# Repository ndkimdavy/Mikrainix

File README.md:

# Mikrainix

Mikrainix is a custom PCB design project for an embedded Linux mini PC based on the **Rockchip RV1106G3 MPU**, featuring integrated AI hardware acceleration and a **Lattice ECP5 FPGA** for programmable logic.

## MPU Specifications

- **CPU:** Single-core ARM Cortex-A7, up to 1.2 GHz.
- **Integrated MCU:** RISC-V architecture.
- **Memory:** 256 MB integrated DDR3L.
- **NPU:** 1 TOPS AI accelerator.
- **Interfaces:** USB 2.0, Ethernet, SDIO, UART, SPI, and I²C.

## FPGA Specifications

- **FPGA:** Lattice ECP5 LFE5U-25F-7BG256C.
- **Communication:** SPI interface with the Rockchip MPU and USB-UART interface.

## Board Architecture

The design also includes:

- An STM32L052 microcontroller for system management and control.
- An ESP32-MINI-1-N4 for Wi-Fi and Bluetooth connectivity.
- A USB-C Power Delivery interface for power management.
- A shared USB port between the MPU and FPGA.
- A dedicated FPGA subsystem with its own power supplies and communication interfaces.

## Project Status

**In progress** — schematic and PCB design phase.

## Author

**Kim Davy NDAYONGEJE**

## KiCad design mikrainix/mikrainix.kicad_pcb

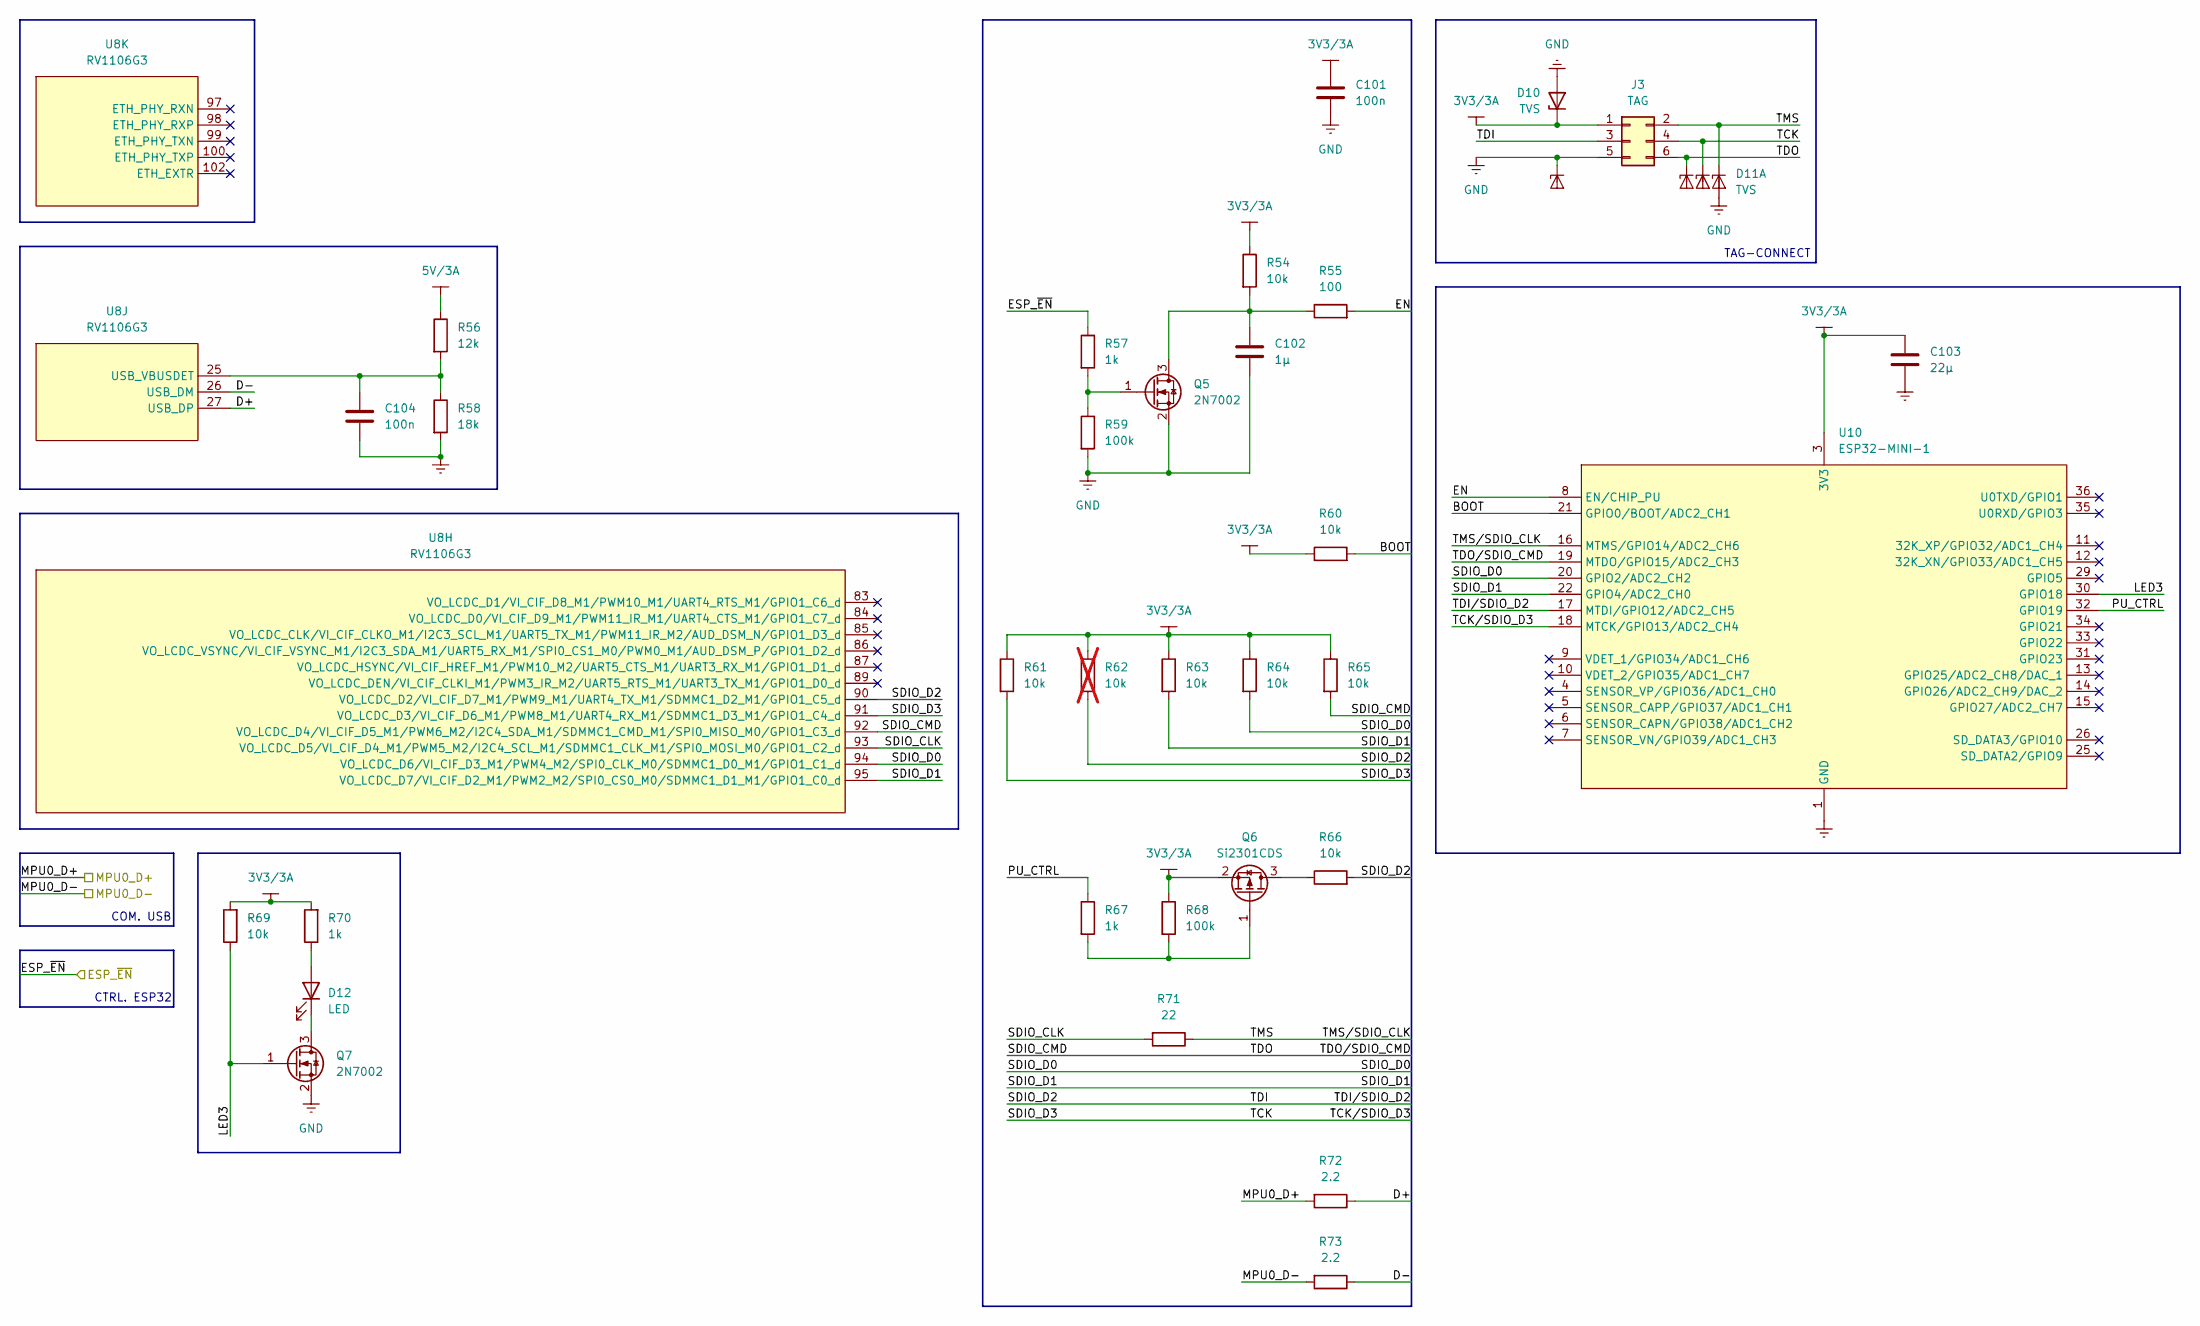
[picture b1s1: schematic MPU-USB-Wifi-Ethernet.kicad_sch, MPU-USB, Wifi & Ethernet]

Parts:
C101, C104: 100n; C_0402_1005Metric
C102: 1µ; C_0603_1608Metric
C103: 22µ; C_1206_3216Metric
D10: TVS; D_SMB; MPN SMLVT3V3
D11: TVS; SOT-353_SC-70-5; MPN ESDALC6V1W5
D12: LED; LED_0603_1608Metric
J3: TAG; Tag-Connect_TC2030-IDC-NL_2x03_P1.27mm_Vertical; MPN TC2030-IDC-NL
Q5, Q7: 2N7002; SOT-23
Q6: Si2301CDS; SOT-23
R54, R60, R61, R63, R64, R65, R66, R69: 10k; R_0402_1005Metric
R55: 100; R_0402_1005Metric
R56: 12k; R_0402_1005Metric
R57, R67, R70: 1k; R_0402_1005Metric
R58: 18k; R_0402_1005Metric
R59, R68: 100k; R_0402_1005Metric
R62: 10k; R_0402_1005Metric; not fitted
R71: 22; R_0402_1005Metric
R72, R73: 2.2; R_0402_1005Metric
U8: RV1106G3; QFN35P1230X1230X90-129N
U10: ESP32-MINI-1

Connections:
3V3/3A: C101.2, C103.1, D10.1 (K), J3.1, Q6.2 (S), R54.1, R60.1, R61.1, R62.1, R63.1, R64.1, R65.1, R68.1, R69.2, R70.2, U10.3 (3V3); also elsewhere on the board
5V/3A: R56.1; also elsewhere on the board
/U_MPU-Clock-Reset-Boot-Gpio/ESP_~EN: R57.1; also elsewhere on the board
/U_MPU-USB-Wifi-Ethernet/BOOT: R60.2, U10.21 (GPIO0/BOOT/ADC2_CH1)
/U_MPU-USB-Wifi-Ethernet/D+: R72.1, U8.27 (USB_DP)
/U_MPU-USB-Wifi-Ethernet/D-: R73.1, U8.26 (USB_DM)
/U_MPU-USB-Wifi-Ethernet/EN: R55.2, U10.8 (EN/CHIP_PU)
/U_MPU-USB-Wifi-Ethernet/LED3: Q7.1 (G), R69.1, U10.30 (GPIO18)
/U_MPU-USB-Wifi-Ethernet/MPU0_D+: R72.2; also elsewhere on the board
/U_MPU-USB-Wifi-Ethernet/MPU0_D-: R73.2; also elsewhere on the board
/U_MPU-USB-Wifi-Ethernet/PU_CTRL: R67.1, U10.32 (GPIO19)
/U_MPU-USB-Wifi-Ethernet/SDIO_CLK: R71.2, U8.93 (VO_LCDC_D5/VI_CIF_D4_M1/PWM5_M2/I2C4_SC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)
/U_MPU-USB-Wifi-Ethernet/SDIO_CMD: D11.4 (K3), J3.6, R65.2, U8.92 (VO_LCDC_D4/VI_CIF_D5_M1/PWM6_M2/I2C4_SD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), U10.19 (MTDO/GPIO15/ADC2_CH3)
/U_MPU-USB-Wifi-Ethernet/SDIO_D0: R64.2, U8.94 (VO_LCDC_D6/VI_CIF_D3_M1/PWM4_M2/SPI0_CL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), U10.20 (GPIO2/ADC2_CH2)
/U_MPU-USB-Wifi-Ethernet/SDIO_D1: R63.2, U8.95 (VO_LCDC_D7/VI_CIF_D2_M1/PWM2_M2/SPI0_CS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), U10.22 (GPIO4/ADC2_CH0)
/U_MPU-USB-Wifi-Ethernet/SDIO_D2: J3.3, R62.2, R66.2, U8.90 (VO_LCDC_D2/VI_CIF_D7_M1/PWM9_M1/UART4_T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), U10.17 (MTDI/GPIO12/ADC2_CH5)
/U_MPU-USB-Wifi-Ethernet/SDIO_D3: D11.3 (K2), J3.4, R61.2, U8.91 (VO_LCDC_D3/VI_CIF_D6_M1/PWM8_M1/UART4_R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), U10.18 (MTCK/GPIO13/ADC2_CH4)
/U_MPU-USB-Wifi-Ethernet/TMS: D11.1 (K1), J3.2, R71.1, U10.16 (MTMS/GPIO14/ADC2_CH6)
GND: C101.1, C102.2, C103.2, C104.1, D10.2 (A), D11.2 (A), D11.5 (K4), J3.5, Q5.2 (S), Q7.2 (S), R58.2, R59.2, U10.1 (GND), U10.2 (GND), U10.27 (GND), U10.38 (GND), U10.39 (GND), U10.40 (GND), U10.41 (GND), U10.42 (GND), U10.43 (GND), U10.44 (GND), U10.45 (GND), U10.46 (GND), U10.47 (GND), U10.48 (GND), U10.49 (GND), U10.50 (GND), U10.51 (GND), U10.52 (GND), U10.53 (GND), U10.54 (GND), U10.55 (GND); also elsewhere on the board
unnamed: D12.2 (A), R70.1
unnamed: D12.1 (K), Q7.3 (D)
unnamed: C102.1, Q5.3 (D), R54.2, R55.1
unnamed: Q5.1 (G), R57.2, R59.1
unnamed: Q6.3 (D), R66.1
unnamed: Q6.1 (G), R67.2, R68.2
unnamed: C104.2, R56.2, R58.1, U8.25 (USB_VBUSDET)

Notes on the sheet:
COM. USB
TAG-CONNECT
CTRL. ESP32

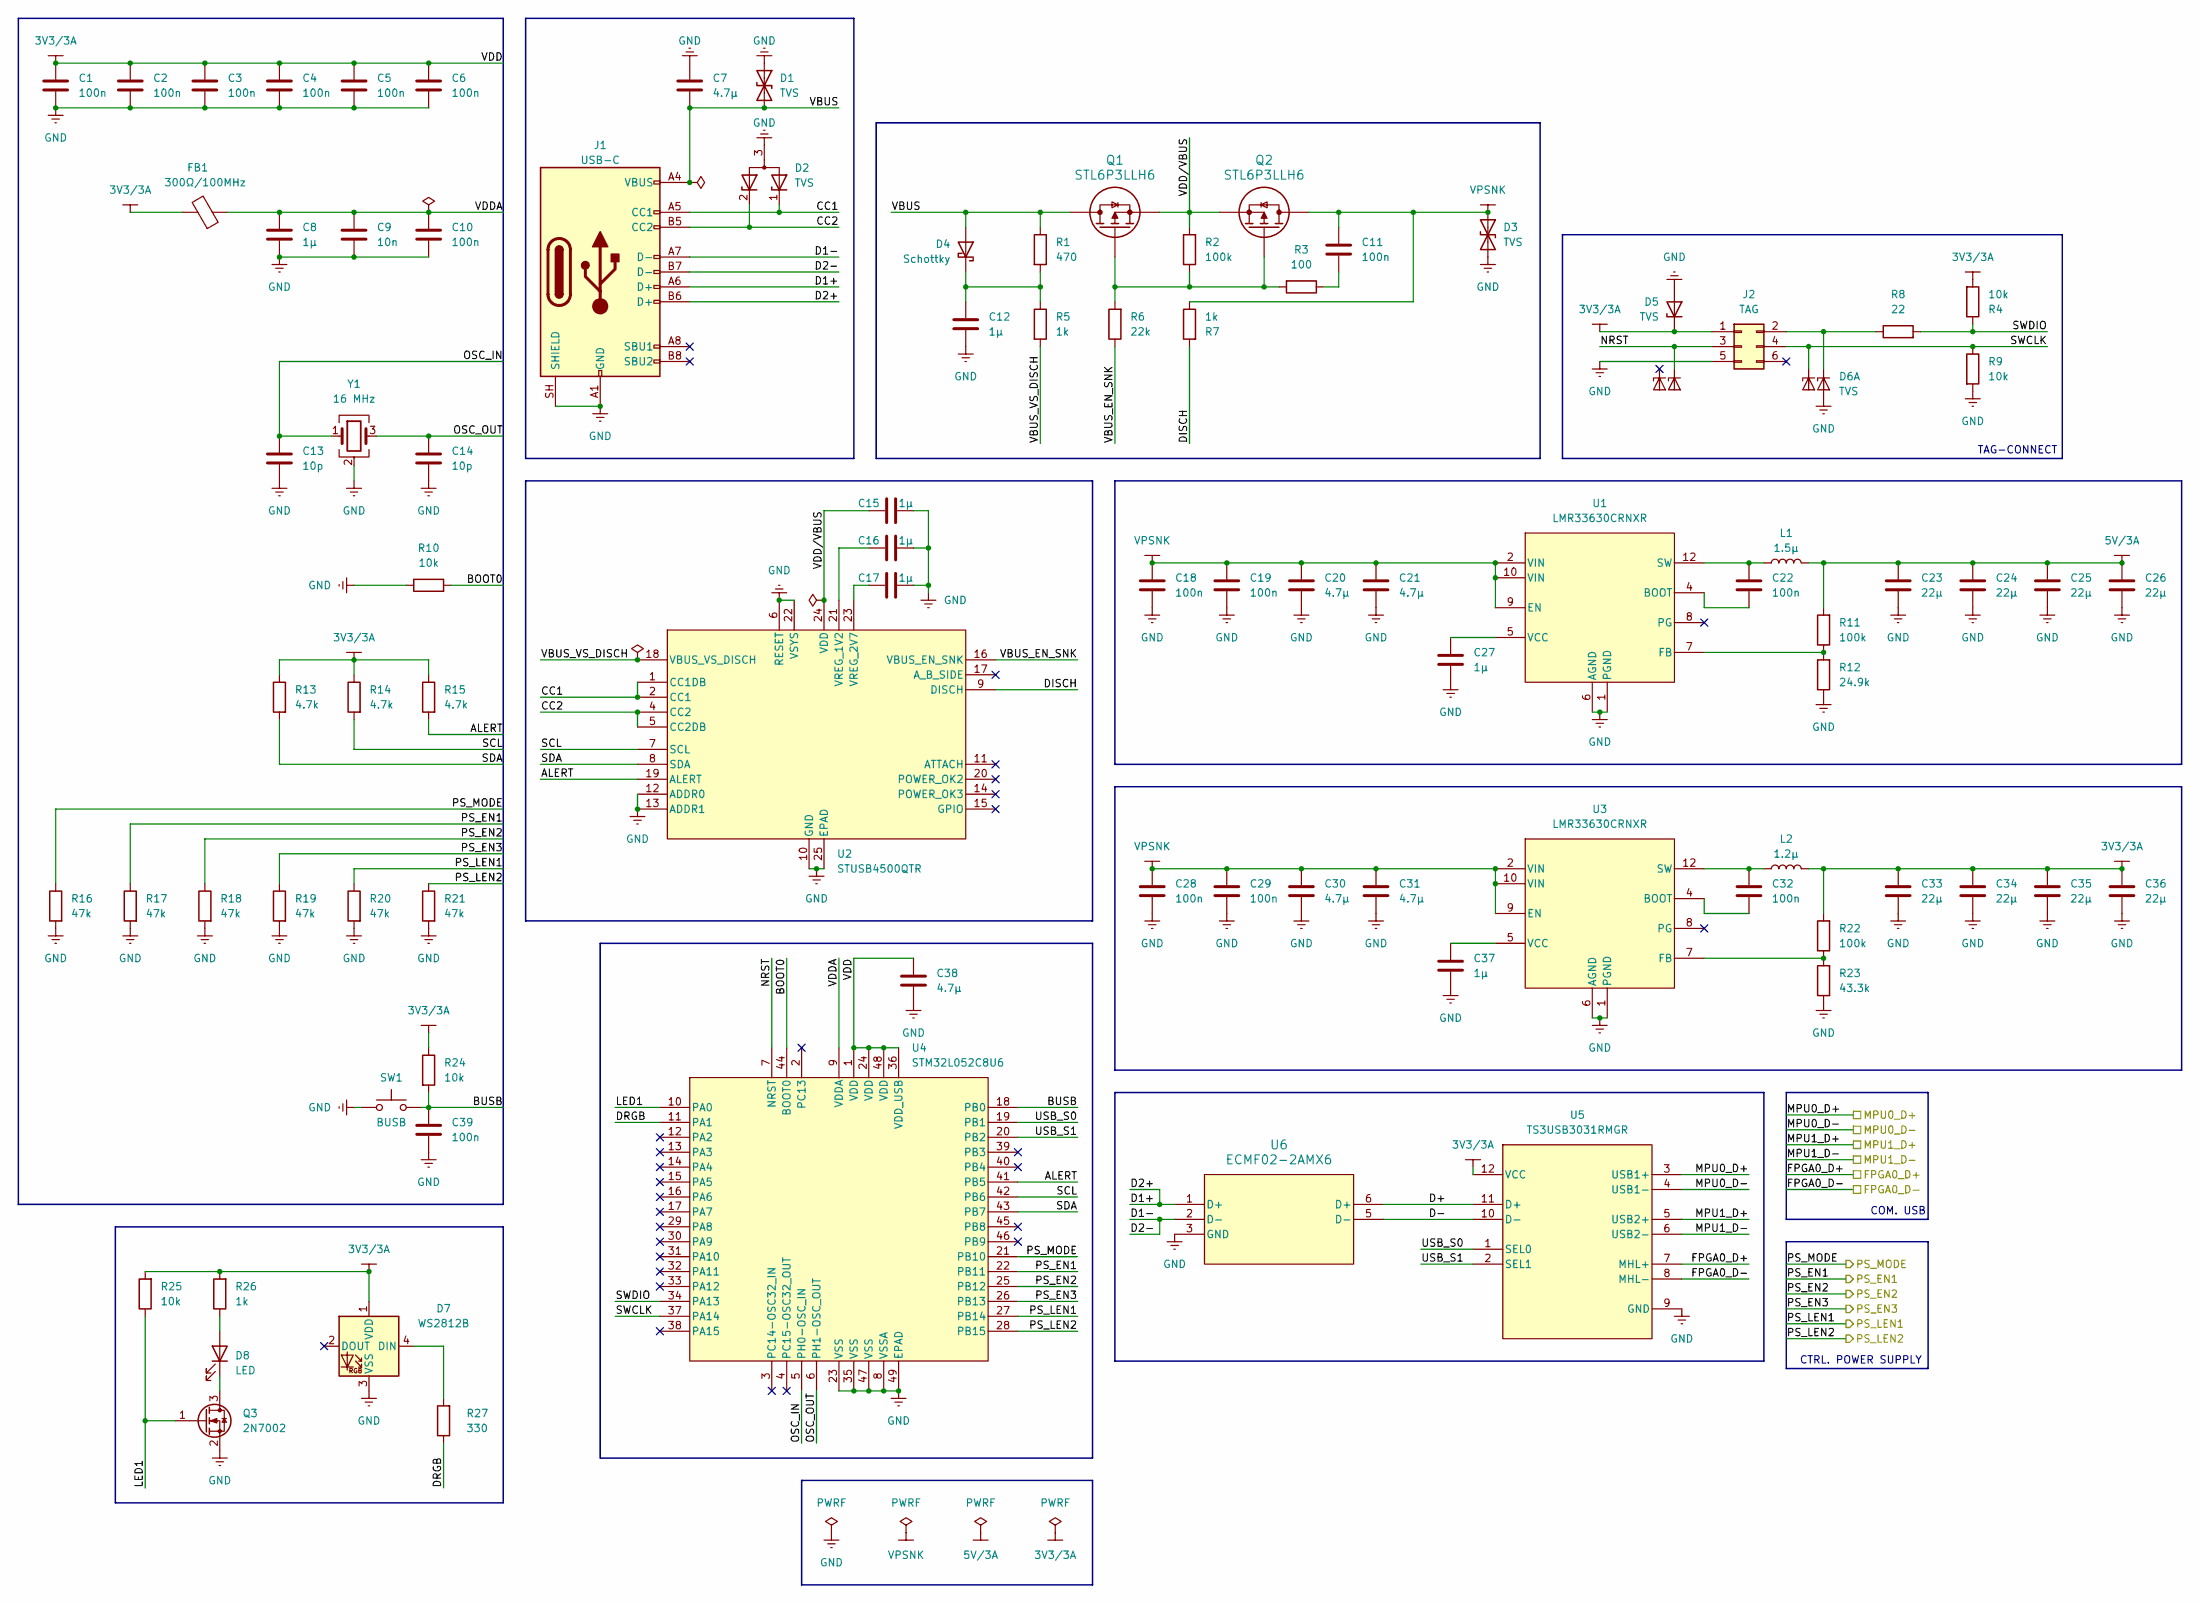
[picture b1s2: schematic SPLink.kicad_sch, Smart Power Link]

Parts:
C1, C2, C3, C4, C5, C6, C10, C39: 100n; C_0402_1005Metric
C7: 4.7µ; C_1206_3216Metric
C8: 1µ; C_0603_1608Metric
C9: 10n; C_0402_1005Metric
C11: 100n; C_0805_2012Metric
C12, C15, C16, C17, C27, C37: 1µ; C_0805_2012Metric
C13, C14: 10p; C_0402_1005Metric; MPN GRM1555C1H100JA01D
C18, C19, C22, C28, C29, C32: 100n; C_0603_1608Metric
C20, C21, C30, C31: 4.7µ; C_1210_3225Metric
C23, C24, C25, C26, C33, C34, C35, C36: 22µ; C_1210_3225Metric
C38: 4.7µ; C_0805_2012Metric
D1, D3: TVS; QFN1610_STM; MPN ESDA25P35-1U1M
D2: TVS; SOT-323_SC-70; MPN ESDA25W
D4: Schottky; D_SOD-323; MPN BAT54JFILM
D5: TVS; D_SMB; MPN SMLVT3V3
D6: TVS; SOT-353_SC-70-5; MPN ESDALC6V1W5
D7: WS2812B; LED_WS2812B_PLCC4_5.0x5.0mm_P3.2mm
D8: LED; LED_0603_1608Metric
FB1: 300Ω/100MHz; L_0603_1608Metric; MPN MMZ1608Y301BTA00
J1: USB-C; USB_C_Receptacle_GCT_USB4105-xx-A_16P_TopMnt_Horizontal; MPN USB4105-GF-A
J2: TAG; Tag-Connect_TC2030-IDC-NL_2x03_P1.27mm_Vertical; MPN TC2030-IDC-NL
L1: 1.5µ; L_Bourns_SRP5030T
L2: 1.2µ; L_Bourns_SRP5030T
Q1, Q2: STL6P3LLH6; POWERFLAT_3P3X3P3_STM
Q3: 2N7002; SOT-23
R1: 470; R_0805_2012Metric
R2: 100k; R_0402_1005Metric
R3: 100; R_0402_1005Metric
R4, R9, R10, R24, R25: 10k; R_0402_1005Metric
R5: 1k; R_0805_2012Metric
R6: 22k; R_0402_1005Metric
R7: 1k; R_1206_3216Metric
R8: 22; R_0402_1005Metric
R11, R22: 100k; R_0603_1608Metric
R12: 24.9k; R_0603_1608Metric
R13, R14, R15: 4.7k; R_0402_1005Metric
R16, R17, R18, R19, R20, R21: 47k; R_0603_1608Metric
R23: 43.3k; R_0603_1608Metric
R26: 1k; R_0402_1005Metric
R27: 330; R_0402_1005Metric
SW1: BUSB; SW_Push_1P1T_NO_CK_KMR2
U1, U3: LMR33630CRNXR; RNX0012B
U2: STUSB4500QTR; QFN24EP_4X4_STM
U4: STM32L052C8U6; UFQFPN-48_STM
U5: TS3USB3031RMGR; RMG12_TEX
U6: ECMF02-2AMX6; QFN-6L_STM
Y1: 16 MHz; Crystal_SMD_3225-4Pin_3.2x2.5mm; MPN ABM8-16.000MHZ-8-D7W-T

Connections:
3V3/3A: C1.1, C2.1, C3.1, C4.1, C5.1, C6.1, C33.1, C34.1, C35.1, C36.1, C38.1, D5.1 (K), D7.1 (VDD), FB1.2, J2.1, L2.2, R4.2, R13.1, R14.1, R15.1, R22.2, R24.1, R25.2, R26.2, U4.1 (VDD), U4.24 (VDD), U4.36 (VDD_USB), U4.48 (VDD), U5.12 (VCC); also elsewhere on the board
5V/3A: C23.1, C24.1, C25.1, C26.1, L1.2, R11.2; also elsewhere on the board
/U_FPGA-Ctrl/FPGA0_D+: U5.7 (MHL+); also elsewhere on the board
/U_FPGA-Ctrl/FPGA0_D-: U5.8 (MHL-); also elsewhere on the board
/U_MPU-Clock-Reset-Boot-Gpio/MPU1_D+: U5.5 (USB2+); also elsewhere on the board
/U_MPU-Clock-Reset-Boot-Gpio/MPU1_D-: U5.6 (USB2-); also elsewhere on the board
/U_MPU-PowerSupply/PS_EN1: R17.1, U4.22 (PB11); also elsewhere on the board
/U_MPU-PowerSupply/PS_EN2: R18.1, U4.25 (PB12); also elsewhere on the board
/U_MPU-PowerSupply/PS_EN3: R19.1, U4.26 (PB13); also elsewhere on the board
/U_MPU-PowerSupply/PS_LEN1: R20.1, U4.27 (PB14); also elsewhere on the board
/U_MPU-PowerSupply/PS_LEN2: R21.1, U4.28 (PB15); also elsewhere on the board
/U_MPU-PowerSupply/PS_MODE: R16.1, U4.21 (PB10); also elsewhere on the board
/U_MPU-USB-Wifi-Ethernet/MPU0_D+: U5.3 (USB1+); also elsewhere on the board
/U_MPU-USB-Wifi-Ethernet/MPU0_D-: U5.4 (USB1-); also elsewhere on the board
/U_SPLink/ALERT: R15.2, U2.19 (ALERT), U4.41 (PB5)
/U_SPLink/BOOT0: R10.2, U4.44 (BOOT0)
/U_SPLink/BUSB: C39.1, R24.2, SW1.2, U4.18 (PB0)
/U_SPLink/CC1: D2.1 (K), J1.A5 (CC1), U2.1 (CC1DB), U2.2 (CC1)
/U_SPLink/CC2: D2.2 (K), J1.B5 (CC2), U2.4 (CC2), U2.5 (CC2DB)
/U_SPLink/D1+: J1.A6 (D+), J1.B6 (D+), U6.1 (D+)
/U_SPLink/D1-: J1.A7 (D-), J1.B7 (D-), U6.2 (D-)
/U_SPLink/D+: U5.11 (D+), U6.6 (D+)
/U_SPLink/D-: U5.10 (D-), U6.5 (D-)
/U_SPLink/DISCH: R7.2, U2.9 (DISCH)
/U_SPLink/DRGB: R27.1, U4.11 (PA1)
/U_SPLink/LED1: Q3.1 (G), R25.1, U4.10 (PA0)
/U_SPLink/NRST: D6.4 (K3), J2.3, U4.7 (NRST)
/U_SPLink/OSC_IN: C13.1, U4.5 (PH0-OSC_IN), Y1.1
/U_SPLink/OSC_OUT: C14.1, U4.6 (PH1-OSC_OUT), Y1.3
/U_SPLink/SCL: R14.2, U2.7 (SCL), U4.42 (PB6)
/U_SPLink/SDA: R13.2, U2.8 (SDA), U4.43 (PB7)
/U_SPLink/SWCLK: D6.3 (K2), J2.4, R9.1, U4.37 (PA14)
/U_SPLink/SWDIO: R4.1, R8.2, U4.34 (PA13)
/U_SPLink/USB_S0: U4.19 (PB1), U5.1 (SEL0)
/U_SPLink/USB_S1: U4.20 (PB2), U5.2 (SEL1)
/U_SPLink/VBUS: C7.2, D1.2 (A2), D4.2 (A), J1.A4 (VBUS), J1.A9 (VBUS), J1.B4 (VBUS), J1.B9 (VBUS), Q1.5 (D), Q1.6 (D), Q1.7 (D), Q1.8 (D), R1.1
/U_SPLink/VBUS_EN_SNK: R6.1, U2.16 (VBUS_EN_SNK)
/U_SPLink/VBUS_VS_DISCH: R5.2, U2.18 (VBUS_VS_DISCH)
/U_SPLink/VDDA: C8.1, C9.1, C10.1, FB1.1, U4.9 (VDDA)
/U_SPLink/VDD/VBUS: C15.1, Q1.1 (S), Q1.2 (S), Q1.3 (S), Q2.1 (S), Q2.2 (S), Q2.3 (S), R2.2, U2.24 (VDD)
GND: C1.2, C2.2, C3.2, C4.2, C5.2, C6.2, C7.1, C8.2, C9.2, C10.2, C12.2, C13.2, C14.2, C15.2, C16.2, C17.2, C18.2, C19.2, C20.2, C21.2, C23.2, C24.2, C25.2, C26.2, C27.2, C28.2, C29.2, C30.2, C31.2, C33.2, C34.2, C35.2, C36.2, C37.2, C38.2, C39.2, D1.1 (A1), D2.3 (A), D3.2 (A2), D5.2 (A), D6.2 (A), D7.3 (VSS), J1.A1 (GND), J1.A12 (GND), J1.B1 (GND), J1.B12 (GND), J1.SH (SHIELD), J2.5, Q3.2 (S), R9.2, R10.1, R12.1, R16.2, R17.2, R18.2, R19.2, R20.2, R21.2, R23.1, SW1.1, U1.1 (PGND), U1.6 (AGND), U1.11 (PGND), U2.6 (RESET), U2.10 (GND), U2.12 (ADDR0), U2.13 (ADDR1), U2.22 (VSYS), U2.25 (EPAD), U3.1 (PGND), U3.6 (AGND), U3.11 (PGND), U4.8 (VSSA), U4.23 (VSS), U4.35 (VSS), U4.47 (VSS), U4.49 (EPAD), U5.9 (GND), U6.3 (GND), Y1.2 (G), Y1.4 (G); also elsewhere on the board
unnamed: C11.2, R3.1
unnamed: C12.1, D4.1 (K), R1.2, R5.1
unnamed: D6.1 (K1), J2.2, R8.1
unnamed: D7.4 (DIN), R27.2
unnamed: D8.2 (A), R26.1
unnamed: D8.1 (K), Q3.3 (D)
unnamed: Q1.4 (G), Q2.4 (G), R2.1, R3.2, R6.2
unnamed: C22.2, U1.4 (BOOT)
unnamed: R11.1, R12.2, U1.7 (FB)
unnamed: C22.1, L1.1, U1.3 (NC), U1.12 (SW)
unnamed: C27.1, U1.5 (VCC)
unnamed: C16.1, U2.21 (VREG_1V2)
unnamed: C17.1, U2.23 (VREG_2V7)
unnamed: C32.2, U3.4 (BOOT)
unnamed: R22.1, R23.2, U3.7 (FB)
unnamed: C32.1, L2.1, U3.3 (NC), U3.12 (SW)
unnamed: C37.1, U3.5 (VCC)
VPSNK: C11.1, C18.1, C19.1, C20.1, C21.1, C28.1, C29.1, C30.1, C31.1, D3.1 (A1), Q2.5 (D), Q2.6 (D), Q2.7 (D), Q2.8 (D), R7.1, U1.2 (VIN), U1.9 (EN), U1.10 (VIN), U3.2 (VIN), U3.9 (EN), U3.10 (VIN)

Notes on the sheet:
COM. USB
TAG-CONNECT
CTRL. POWER SUPPLY

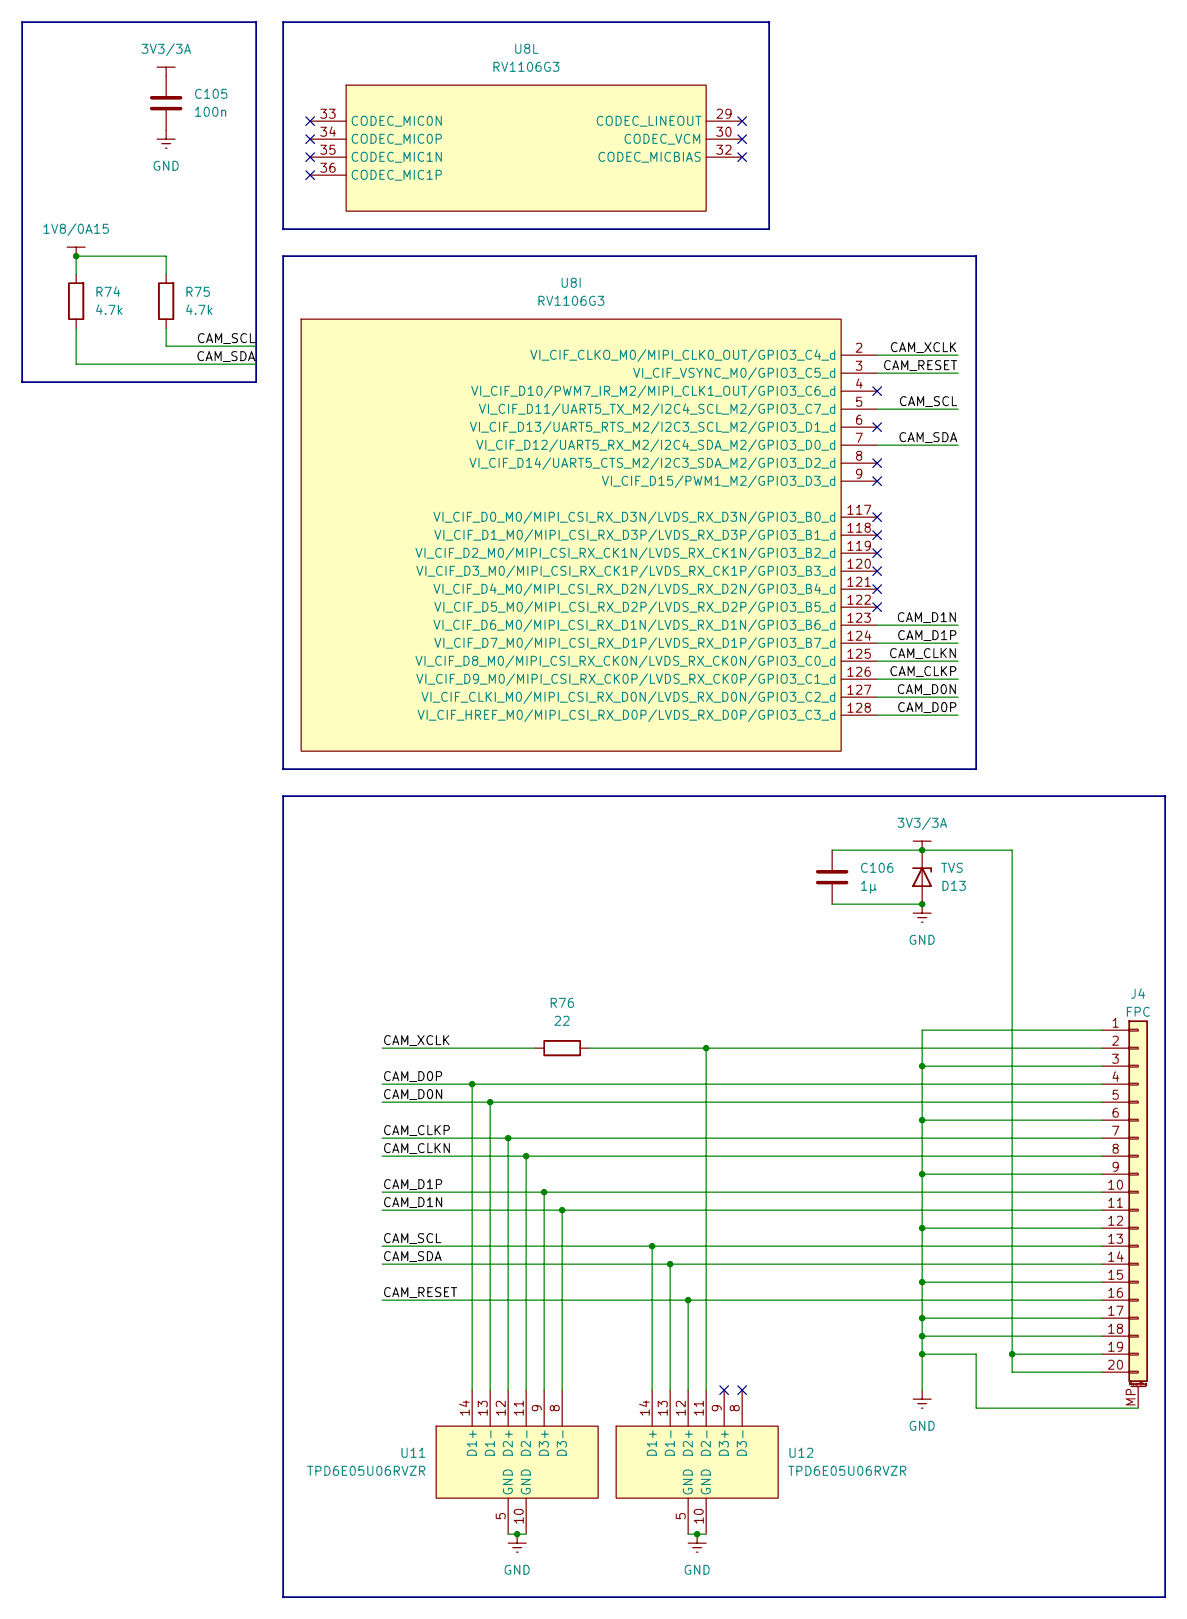
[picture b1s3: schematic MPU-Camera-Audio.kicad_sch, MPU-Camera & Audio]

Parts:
C105: 100n; C_0402_1005Metric
C106: 1µ; C_0603_1608Metric
D13: TVS; D_SMB; MPN SMLVT3V3
J4: FPC; Hirose_FH12-20S-0.5SH_1x20-1MP_P0.50mm_Horizontal
R74, R75: 4.7k; R_0402_1005Metric
R76: 22; R_0402_1005Metric
U8: RV1106G3; QFN35P1230X1230X90-129N
U11, U12: TPD6E05U06RVZR; RVZ0014A

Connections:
1V8/0A15: R74.2, R75.2; also elsewhere on the board
3V3/3A: C105.1, C106.1, D13.1 (K), J4.19, J4.20; also elsewhere on the board
/U_MPU-Camera-Audio/CAM_CLKN: J4.8, U8.125 (VI_CIF_D8_M0/MIPI_CSI_RX_CK0N/LVDS_RX_C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), U11.11 (D2-)
/U_MPU-Camera-Audio/CAM_CLKP: J4.7, U8.126 (VI_CIF_D9_M0/MIPI_CSI_RX_CK0P/LVDS_RX_C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), U11.12 (D2+)
/U_MPU-Camera-Audio/CAM_D0N: J4.5, U8.127 (VI_CIF_CLKI_M0/MIPI_CSI_RX_D0N/LVDS_RX_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), U11.13 (D1-)
/U_MPU-Camera-Audio/CAM_D0P: J4.4, U8.128 (VI_CIF_HREF_M0/MIPI_CSI_RX_D0P/LVDS_RX_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), U11.14 (D1+)
/U_MPU-Camera-Audio/CAM_D1N: J4.11, U8.123 (VI_CIF_D6_M0/MIPI_CSI_RX_D1N/LVDS_RX_D1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), U11.8 (D3-)
/U_MPU-Camera-Audio/CAM_D1P: J4.10, U8.124 (VI_CIF_D7_M0/MIPI_CSI_RX_D1P/LVDS_RX_D1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), U11.9 (D3+)
/U_MPU-Camera-Audio/CAM_RESET: J4.16, U8.3 (VI_CIF_VSYNC_M0/GPIO3_C5_d), U12.12 (D2+)
/U_MPU-Camera-Audio/CAM_SCL: J4.13, R75.1, U8.5 (VI_CIF_D11/UART5_TX_M2/I2C4_SCL_M2/GPIO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), U12.14 (D1+)
/U_MPU-Camera-Audio/CAM_SDA: J4.14, R74.1, U8.7 (VI_CIF_D12/UART5_RX_M2/I2C4_SDA_M2/GPIO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), U12.13 (D1-)
/U_MPU-Camera-Audio/CAM_XCLK: R76.1, U8.2 (VI_CIF_CLKO_M0/MIPI_CLK0_OUT/GPIO3_C4_d)
GND: C105.2, C106.2, D13.2 (A), J4.1, J4.3, J4.6, J4.9, J4.12, J4.15, J4.17, J4.18, J4.MP (MountPin), U11.5 (GND), U11.10 (GND), U12.5 (GND), U12.10 (GND); also elsewhere on the board
unnamed: J4.2, R76.2, U12.11 (D2-)

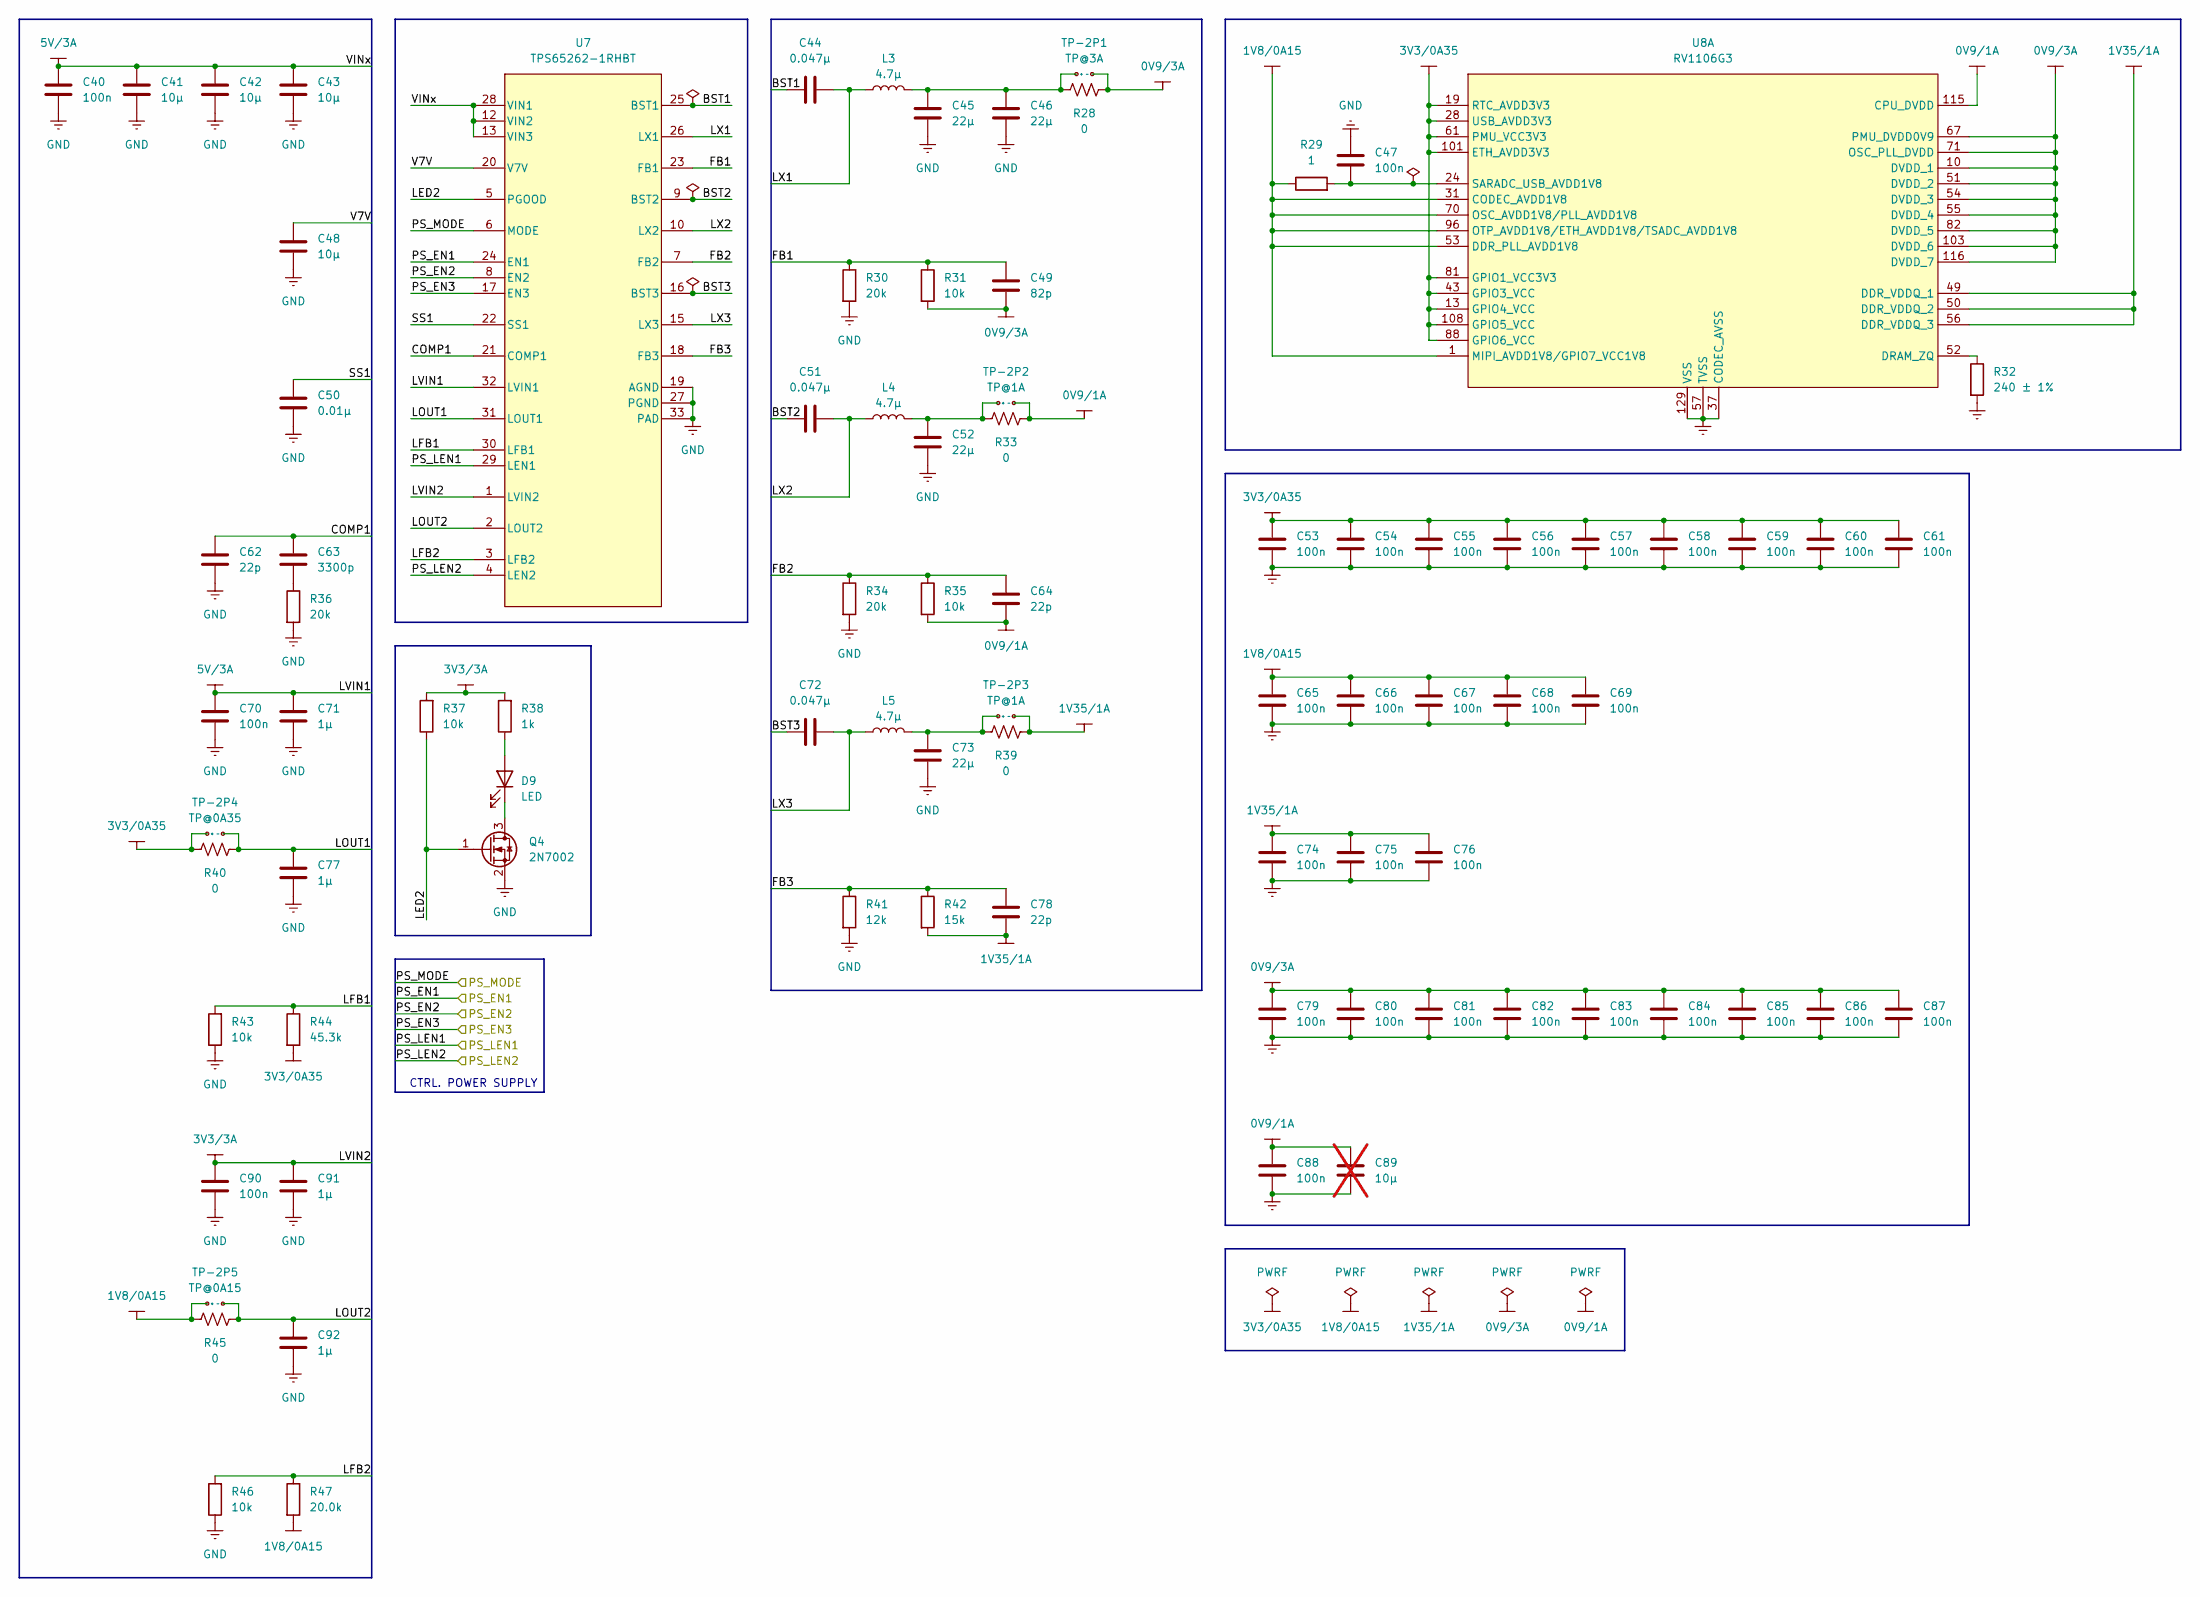
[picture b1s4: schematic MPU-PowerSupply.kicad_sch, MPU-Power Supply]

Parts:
C40, C70, C90: 100n; C_0603_1608Metric
C41, C42, C43, C48: 10µ; C_1206_3216Metric
C44, C51, C72: 0.047µ; C_0603_1608Metric
C45, C46, C52, C73: 22µ; C_1206_3216Metric
C47, C53, C54, C55, C56, C57, C58, C59, C60, C61, C65, C66, C67, C68, C69, C74, C75, C76, C79, C80, C81, C82, C83, C84, C85, C86, C87, C88: 100n; C_0402_1005Metric
C49: 82p; C_0402_1005Metric
C50: 0.01µ; C_0402_1005Metric
C62, C64, C78: 22p; C_0402_1005Metric
C63: 3300p; C_0402_1005Metric
C71, C77, C91, C92: 1µ; C_0603_1608Metric
C89: 10µ; C_0805_2012Metric; not fitted
D9: LED; LED_0603_1608Metric
L3: 4.7µ; L_Bourns_SRP5030T
L4, L5: 4.7µ; L_Bourns-SRN4018
Q4: 2N7002; SOT-23
R28, R33, R39, R40, R45: 0; R_0603_1608Metric
R29: 1; R_0402_1005Metric
R30, R34, R36: 20k; R_0402_1005Metric
R31, R35, R37, R43, R46: 10k; R_0402_1005Metric
R32: 240 ± 1%; R_0402_1005Metric
R38: 1k; R_0402_1005Metric
R41: 12k; R_0402_1005Metric
R42: 15k; R_0402_1005Metric
R44: 45.3k; R_0402_1005Metric
R47: 20.0k; R_0402_1005Metric
TP-2P1: TP@3A; TESTPOINT_x2P
TP-2P2, TP-2P3: TP@1A; TESTPOINT_x2P
TP-2P4: TP@0A35; TESTPOINT_x2P
TP-2P5: TP@0A15; TESTPOINT_x2P
U7: TPS65262-1RHBT; RHB0032E_NV
U8: RV1106G3; QFN35P1230X1230X90-129N

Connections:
0V9/1A: C64.2, C88.1, C89.1, R33.2, R35.2, TP-2P2.2 (-), U8.115 (CPU_DVDD)
0V9/3A: C49.2, C79.1, C80.1, C81.1, C82.1, C83.1, C84.1, C85.1, C86.1, C87.1, R28.2, R31.2, TP-2P1.2 (-), U8.10 (DVDD_1), U8.51 (DVDD_2), U8.54 (DVDD_3), U8.55 (DVDD_4), U8.67 (PMU_DVDD0V9), U8.71 (OSC_PLL_DVDD), U8.82 (DVDD_5), U8.103 (DVDD_6), U8.116 (DVDD_7)
1V8/0A15: C65.1, C66.1, C67.1, C68.1, C69.1, R29.1, R45.1, R47.2, TP-2P5.1 (+), U8.1 (MIPI_AVDD1V8/GPIO7_VCC1V8), U8.31 (CODEC_AVDD1V8), U8.53 (DDR_PLL_AVDD1V8), U8.70 (OSC_AVDD1V8/PLL_AVDD1V8), U8.96 (OTP_AVDD1V8/ETH_AVDD1V8/TSADC_AVDD1V8); also elsewhere on the board
1V35/1A: C74.1, C75.1, C76.1, C78.2, R39.2, R42.2, TP-2P3.2 (-), U8.49 (DDR_VDDQ_1), U8.50 (DDR_VDDQ_2), U8.56 (DDR_VDDQ_3)
3V3/0A35: C53.1, C54.1, C55.1, C56.1, C57.1, C58.1, C59.1, C60.1, C61.1, R40.1, R44.2, TP-2P4.1 (+), U8.13 (GPIO4_VCC), U8.19 (RTC_AVDD3V3), U8.28 (USB_AVDD3V3), U8.43 (GPIO3_VCC), U8.61 (PMU_VCC3V3), U8.81 (GPIO1_VCC3V3), U8.88 (GPIO6_VCC), U8.101 (ETH_AVDD3V3), U8.108 (GPIO5_VCC); also elsewhere on the board
3V3/3A: C90.1, C91.1, R37.2, R38.2, U7.1 (LVIN2); also elsewhere on the board
5V/3A: C40.1, C41.1, C42.1, C43.1, C70.1, C71.1, U7.12 (VIN2), U7.13 (VIN3), U7.28 (VIN1), U7.32 (LVIN1); also elsewhere on the board
/U_MPU-PowerSupply/BST1: C44.1, U7.25 (BST1)
/U_MPU-PowerSupply/BST2: C51.1, U7.9 (BST2)
/U_MPU-PowerSupply/BST3: C72.1, U7.16 (BST3)
/U_MPU-PowerSupply/COMP1: C62.2, C63.2, U7.21 (COMP1)
/U_MPU-PowerSupply/FB1: C49.1, R30.1, R31.1, U7.23 (FB1)
/U_MPU-PowerSupply/FB2: C64.1, R34.1, R35.1, U7.7 (FB2)
/U_MPU-PowerSupply/FB3: C78.1, R41.1, R42.1, U7.18 (FB3)
/U_MPU-PowerSupply/LED2: Q4.1 (G), R37.1, U7.5 (PGOOD)
/U_MPU-PowerSupply/LFB1: R43.2, R44.1, U7.30 (LFB1)
/U_MPU-PowerSupply/LFB2: R46.2, R47.1, U7.3 (LFB2)
/U_MPU-PowerSupply/LOUT1: C77.1, R40.2, TP-2P4.2 (-), U7.31 (LOUT1)
/U_MPU-PowerSupply/LOUT2: C92.1, R45.2, TP-2P5.2 (-), U7.2 (LOUT2)
/U_MPU-PowerSupply/LX1: C44.2, L3.1, U7.26 (LX1)
/U_MPU-PowerSupply/LX2: C51.2, L4.1, U7.10 (LX2)
/U_MPU-PowerSupply/LX3: C72.2, L5.1, U7.15 (LX3)
/U_MPU-PowerSupply/PS_EN1: U7.24 (EN1); also elsewhere on the board
/U_MPU-PowerSupply/PS_EN2: U7.8 (EN2); also elsewhere on the board
/U_MPU-PowerSupply/PS_EN3: U7.17 (EN3); also elsewhere on the board
/U_MPU-PowerSupply/PS_LEN1: U7.29 (LEN1); also elsewhere on the board
/U_MPU-PowerSupply/PS_LEN2: U7.4 (LEN2); also elsewhere on the board
/U_MPU-PowerSupply/PS_MODE: U7.6 (MODE); also elsewhere on the board
/U_MPU-PowerSupply/SS1: C50.1, U7.22 (SS1)
/U_MPU-PowerSupply/V7V: C48.1, U7.20 (V7V)
GND: C40.2, C41.2, C42.2, C43.2, C45.2, C46.2, C47.1, C48.2, C50.2, C52.2, C53.2, C54.2, C55.2, C56.2, C57.2, C58.2, C59.2, C60.2, C61.2, C62.1, C65.2, C66.2, C67.2, C68.2, C69.2, C70.2, C71.2, C73.2, C74.2, C75.2, C76.2, C77.2, C79.2, C80.2, C81.2, C82.2, C83.2, C84.2, C85.2, C86.2, C87.2, C88.2, C89.2, C90.2, C91.2, C92.2, Q4.2 (S), R30.2, R32.2, R34.2, R36.2, R41.2, R43.1, R46.1, U7.11 (PGND), U7.14 (PGND), U7.19 (AGND), U7.27 (PGND), U7.33 (PAD), U8.37 (CODEC_AVSS), U8.57 (TVSS), U8.129 (VSS); also elsewhere on the board
unnamed: C63.1, R36.1
unnamed: D9.2 (A), R38.1
unnamed: D9.1 (K), Q4.3 (D)
unnamed: C45.1, C46.1, L3.2, R28.1, TP-2P1.1 (+)
unnamed: C52.1, L4.2, R33.1, TP-2P2.1 (+)
unnamed: C73.1, L5.2, R39.1, TP-2P3.1 (+)
unnamed: R32.1, U8.52 (DRAM_ZQ)
unnamed: C47.2, R29.2, U8.24 (SARADC_USB_AVDD1V8)

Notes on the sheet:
CTRL. POWER SUPPLY
